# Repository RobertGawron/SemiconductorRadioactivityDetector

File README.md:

# Semiconductor Radioactivity Detector

## Summary

There are many ways to measure radioactivity levels. Semiconductor detectors sense interactions between ionizing radiation and a p-n junction. Since most hobbyists use Geiger-Muller-based detectors (which are lamp-based devices, not semiconductors), I think it's a cool idea to explore this semiconductor-based approach.

## System Architecture

## Additional sub-components used

### Hardware Data Logger

A pulse counter based on the STM32 and ESP chips that can send the measurements via WiFi for further processing, store them on an SD card, or display them to the user. This is an [open-source and open-hardware project that I created, available on GitHub.](https://github.com/RobertGawron/HardwareDataLogger)

### Auxiliary Board (Power Supply + Logic Level Converter)

An auxiliary board was developed later on to fix things that weren’t included on the original board (because it's easier to add a new board than to rework the whole device). This board isn’t really a successful one, but it does its job. It has:

**12V power supply (powered from a 15V wall adapter).** The device needs a very low-noise power supply. Originally, it was powered by a high-quality lab power supply. However, to make it more versatile, I tried using a cheap Chinese power supply and add a board with a power regulator. 

In the first revision, I chose the NCP1117 stabiliser, but it was too noisy. This caused the sensor's output to oscillate randomly, which made the device rather pointless. I made it work by adding plenty of capacitors on the input and output, though this was always a temporary solution. 

In the new version, I will be replacing it with the TPS7A2601DRVR.

**Logic level converter,** to convert logic levels from 12V (high) and 0V (low)—as output by the sensor—to 3.3V (high) and 0V (low), which is standard for STM32 and cheap Chinese logic analyzers. 

In the first version, I just used an open-collector configuration, but this made the device unable to work directly with cheap 3.3V logic analyzers, which need either 0V (low state) or 3.3V (high state).

In the new version, I added a cheap 3.3V stabiliser to provide the correct high state.

## Hardware

All hardware was done using KiCad.

The sensor assembly needs care, as this device is extremely sensitive; [more details are presented in this README.](./Hardware/SemiconductorRadioactivityDetector/README.md)

The sensor circuit is shown below.

The new design of the auxiliary board is shown below, integrated with the whole device. It's the small PCB on the right side of the image. The render was done using Blender.

Circuit of the Auxiliary Board is shown below.

## Mechanic

Before ordering PCBs and the 3D print for the auxiliary holder, how could I be sure everything would fit? Instead of redoing things many times, I took the model of the old PCB, the new PCB that would be the addition to it, the 3D holder, and the metal enclosure (which is a popular consumer enclosure), placed them all accordingly in Blender, and checked if everything fit.

[The needed tools and the workflow are presented in this README.](./Mechanic/README.md)

## Software

[There are some Python and R scripts available](./Software/DataAcquisition/) for gathering data from the device. These were developed during the initial testing phase and may still be useful due to their simplicity.

In the future, the goal is to transition to using the [Hardware Data Logger](https://github.com/RobertGawron/HardwareDataLogger), which provides a more versatile and efficient way to collect measurements.

## Project History

 * [First Unsuccessful Attempts](https://robertgawron.blogspot.com/2016/12/semiconductor-radioactivity-detector.html)
semiconductor-radioactivity-detector.html) - the biggest issue was the lack of proper shielding. Due to the extremely high amplification levels, the device either failed to function or began oscillating uncontrollably without adequate shielding.
* [First Working Version](https://robertgawron.blogspot.com/2019/02/semiconductor-radioactivity-detector.html) - this was a simplified version of the current project. It lacked both polarization voltage and an ADC converter, but it laid the foundation for further improvements.

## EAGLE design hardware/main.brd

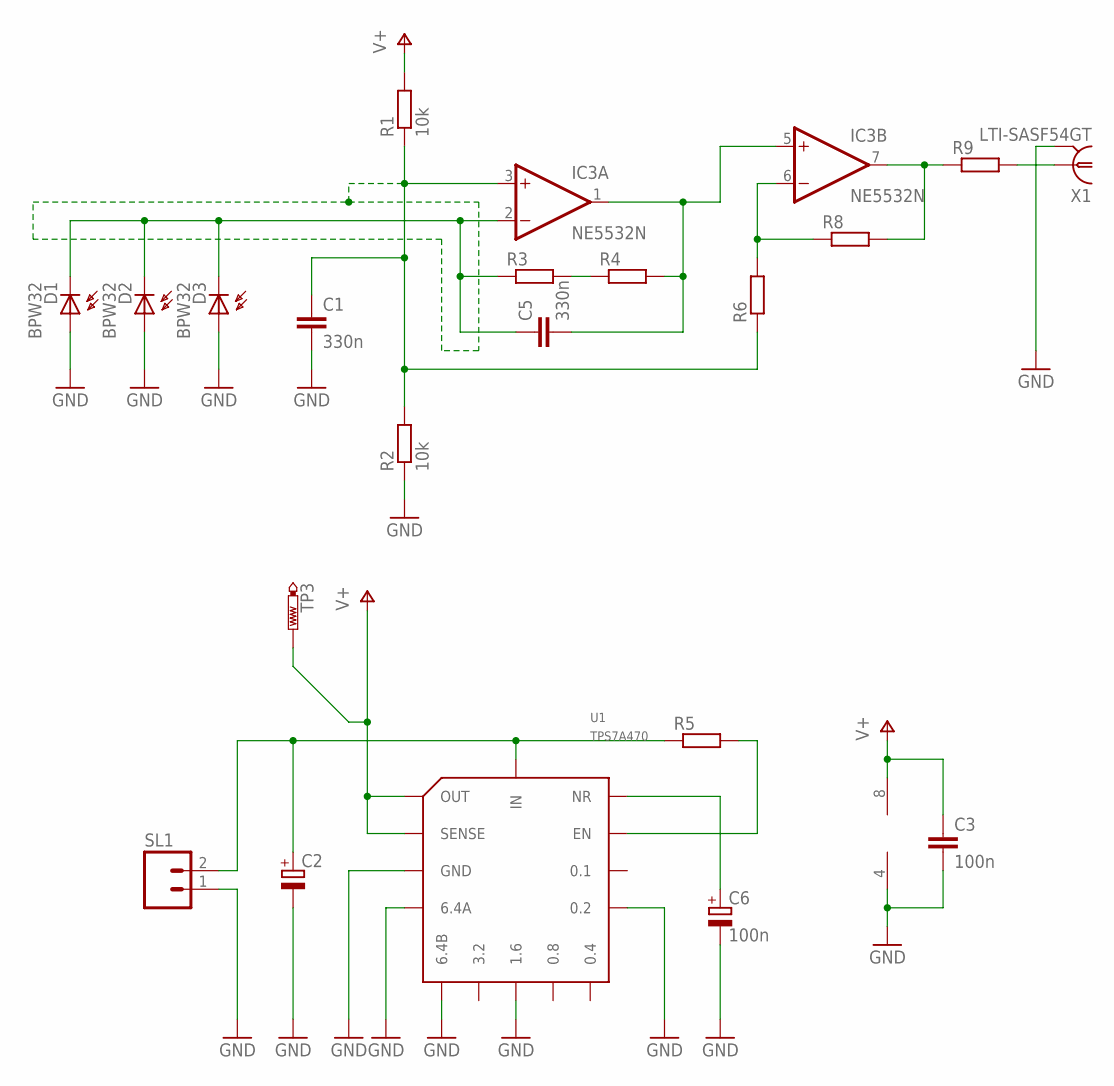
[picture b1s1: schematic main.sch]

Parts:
C1: 330n; C0805
C2: CPOL-EUT/3528-12R; T/3528-12R
C3: 100n; C0805
C5: 330n; C1206
C6: 100n; A/3216-18W
D1, D2, D3: BPW32
IC3: NE5532N; DIL08
R1, R2: 10k; R0805
R3, R4: R-EU_MELF0204W; MINI_MELF-0204W
R5: R-EU_M1206; M1206
R6: R-EU_R0805; R0805
R8: R-EU_M0805; M0805
R9: R-EU_0204/2V; 0204V
SL1: M02; 02P
TP3: PTR1TP12R; TP12R
U1: TPS7A470; S-PVQFN-N20
X1: LTI-SASF54GT

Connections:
GND: C1.2, C2.-, C3.2, C6.-, D1.A, D2.A, D3.A, IC3.4 (V-), R2.1, SL1.1, U1.2 (GND), U1.4 (6.4A), U1.5 (6.4B), U1.7 (GND), U1.8 (1.6), U1.11 (0.2), U1.17 (GND), U1.18 (GND), U1.19 (GND), U1.EXP (GND), X1.2, X1.3 (2), X1.4 (2), X1.5 (2)
unnamed: C5.2, IC3.1 (OUT), IC3.5 (+IN), R4.2
unnamed: IC3.6 (-IN), R6.2, R8.1
unnamed: R3.2, R4.1
unnamed: C5.1, D1.K (C), D2.K (C), D3.K (C), IC3.2 (-IN), R3.1
unnamed: C6.+, U1.14 (NR)
unnamed: R5.2, U1.13 (EN)
unnamed: C1.1, IC3.3 (+IN), R1.1, R2.2, R6.1
unnamed: C2.+, R5.1, SL1.2, U1.15 (IN), U1.16 (IN)
unnamed: IC3.7 (OUT), R8.2, R9.1
unnamed: R9.2, X1.1
V+: C3.1, IC3.8 (V+), R1.2, TP3.TP, U1.1 (OUT), U1.3 (SENSE), U1.20 (OUT)

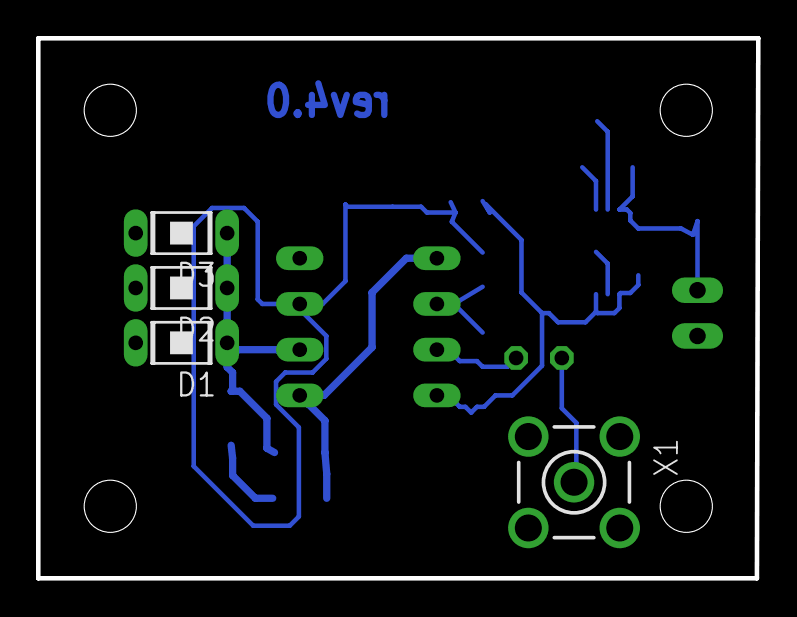
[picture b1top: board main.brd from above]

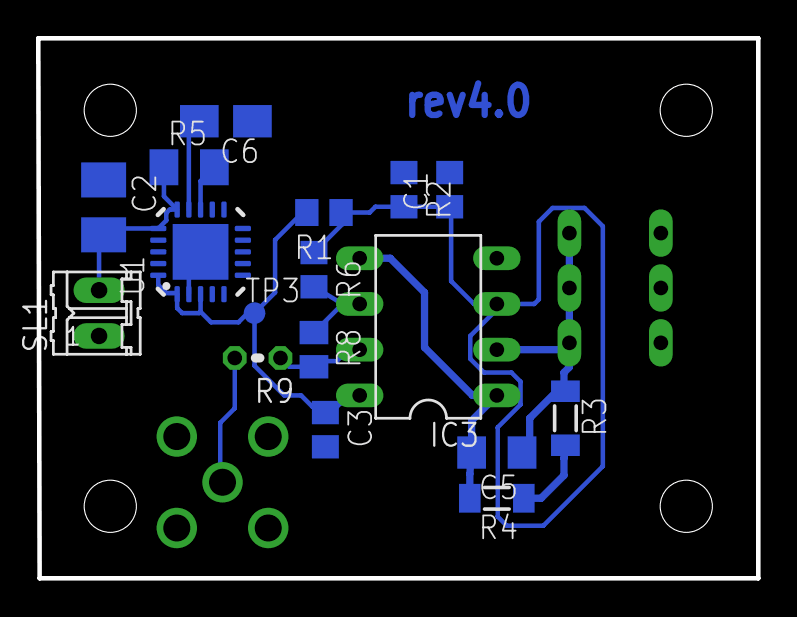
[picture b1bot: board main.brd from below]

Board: 2 copper layers, 40.0 x 30.0 mm, 21 parts (17 on the bottom side), 12 nets.

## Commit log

2017-01-14 Initial commit.
2018-05-27 Removed old obsolete version.
2018-05-27 New HW version.
2018-09-15 cleanup in docs
2018-09-18 pcb fixes before sending to factory
2018-09-19 final touch before ordering pcb
2018-09-19 Create LICENSE
2019-02-16 initial versionwq
2019-02-16 added files to parse results
2019-02-16 scripts to create diagrams
2019-02-17 automated .png generation
2019-02-17 added architecture of raspbbery pi app
2019-02-24 fixed missing libraries
2019-02-24 last touch before sending to pcb factory
2019-02-24 added clearance
2019-05-03 fixes after hw assembly and tests
2019-06-04 removed junk files, added gitignore
2019-08-11 add sections to readme
2019-08-11 fix #18
2019-08-11 fix #23
2019-08-11 forder structure cleanup
2019-08-11 better folder name
2019-08-11 unified names with other my repos
2019-08-11 reworked architecture diagram
2019-08-11 fix #19 #20
2019-08-11 infor about sw architecture
2019-08-11 build latex documents
2019-08-11 added CI
2019-08-11 fix to work with travis
2019-08-11 fix typos
2019-08-11 more redable
2019-08-11 fix #34
2019-09-08 fix #37
2019-09-08 sensor moved to its own subdirectory
2019-09-08 added logic converter project
2020-06-01 add basic simulator of digital filters
2020-10-15 Squashed 'Software/HardwareDataLogger/' content from commit 37d90c3
    git-subtree-dir: Software/HardwareDataLogger
    git-subtree-split: 37d90c36ef6dff2428dff3a75682a6a990aea3fe
2020-10-15 exclude external repo from language statistics
2020-10-17 remove old subrepo version
2020-10-17 Squashed 'Software/HardwareDataLogger/' content from commit 36e64a0
    git-subtree-dir: Software/HardwareDataLogger
    git-subtree-split: 36e64a0b74689bc3145da8180f2f13aac98a8adf
2020-10-22 move from travis to guthub actions
2020-10-22 add README.md
2020-10-22 docs update
2020-10-23 link build status to project's build section
2020-10-24 move (for diagrams) from .png to .svg
2020-10-24 move (for diagrams) from .png to .svg - add missing update
2020-10-24 Squashed 'Software/HardwareDataLogger/' changes from 36e64a0..dc3c36e
2020-10-24 Squashed 'Software/HardwareDataLogger/' changes from 36e64a0..dc3c36e
    dc3c36e Merge pull request #21 from RobertGawron/develop
    a8342c6 Merge pull request #20 from RobertGawron/feature/add_contionous_integration
    304d8cd fix c linter issues
    4a7e1a6 Merge pull request #19 from RobertGawron/develop
    1880f22 Merge pull request #18 from RobertGawron/feature/add_contionous_integration
    7c2c33d exclude external libs from repo programming language statistics
2020-11-06 Fix grammar mistakes (found by Code Spell Checker add-on in VSCode). (fix #62)
2020-11-06 Squashed 'Software/HardwareDataLogger/' changes from dc3c36e..58e2b47
    58e2b47 Merge pull request #24 from RobertGawron/develop
    74d7174 Merge pull request #23 from RobertGawron/fix/remove_gammar_mistakes
    8752828 Fix grammar mistakes (found by Code Spell Checker add-on in VSCode). (fix #22)
    git-subtree-dir: Software/HardwareDataLogger
    git-subtree-split: 58e2b477f2824c01ec6d98d952829f0472e2d4a0
2024-09-15 transition to kicad8 and docs cleanup
2025-06-08 auxiliary board rev1.0
2025-09-14 auxiliary board rev2 + its 3d printed holder
2026-02-07 remove obsolete files
